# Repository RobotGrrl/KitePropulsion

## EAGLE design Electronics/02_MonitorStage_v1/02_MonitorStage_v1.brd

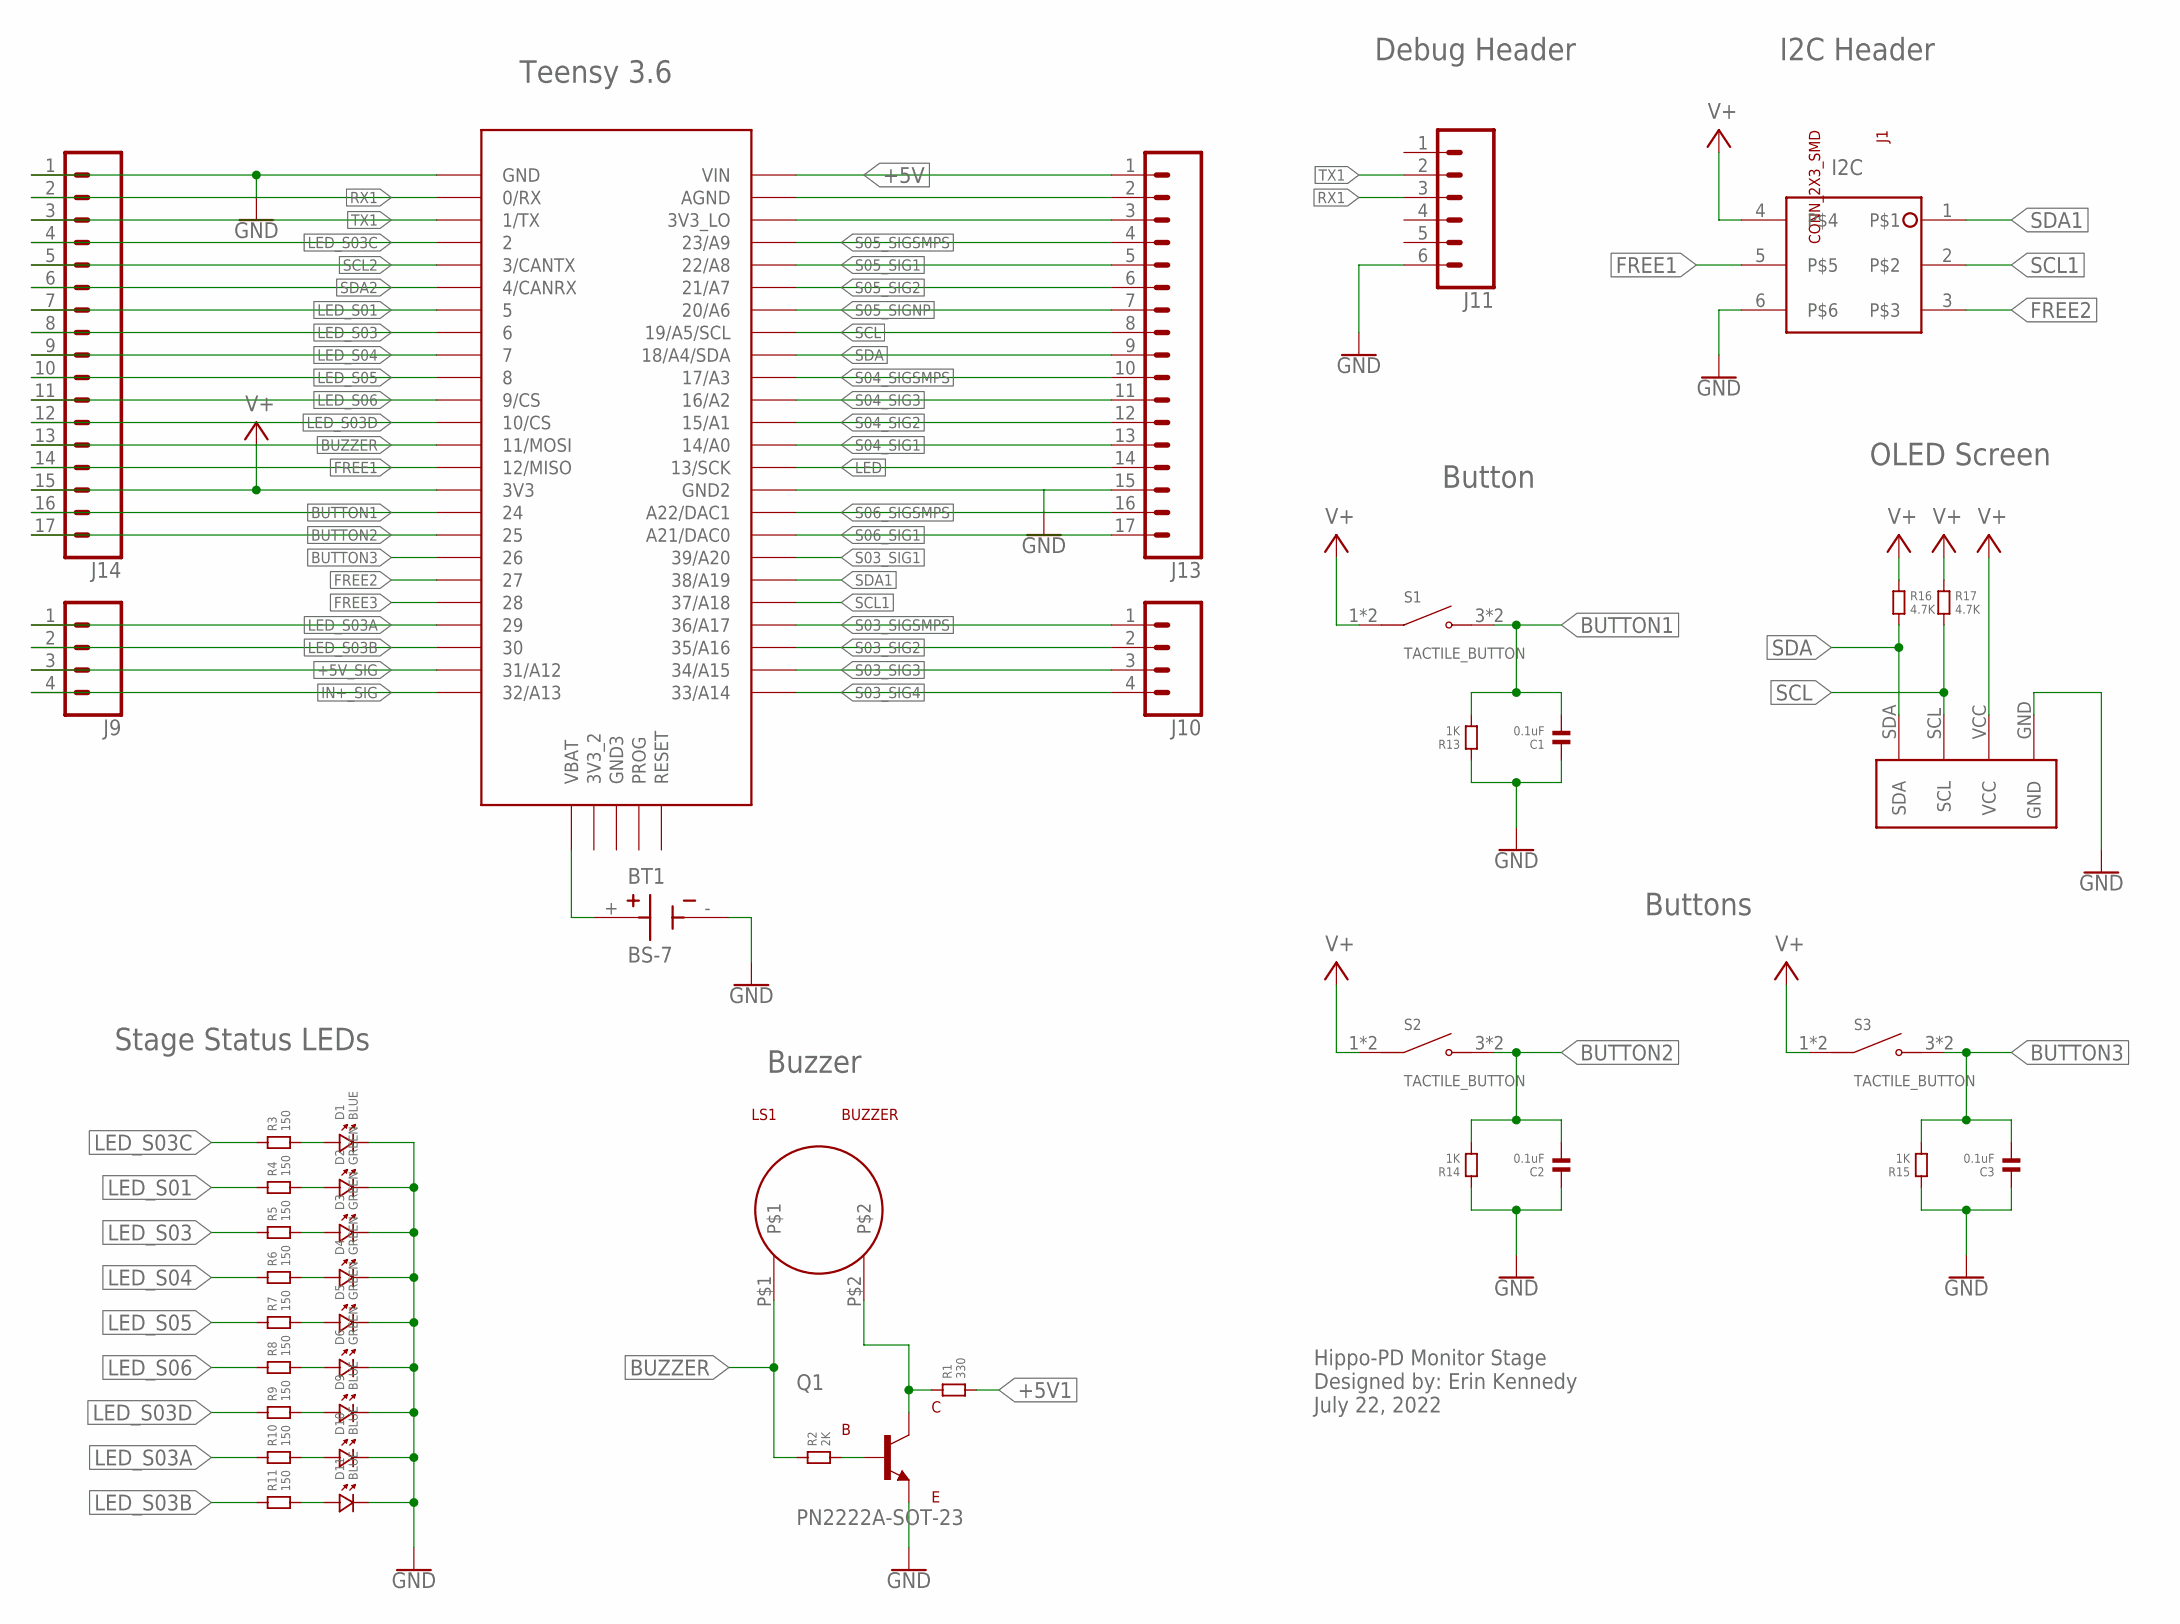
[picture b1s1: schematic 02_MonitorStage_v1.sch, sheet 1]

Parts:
BT1: BS-7; BAT_BS-7
C1, C2, C3: 0.1uF; 1206
D1, D9, D10, D11: BLUE; 1206.LED
D2, D3, D4, D5, D6: GREEN; 1206.LED
J1: CONN_2X3_SMD; 2X3_SMD_CONNECTOR
J9, J10: CONN_04; 1X04
J11: CONN_06; 1X06-SMD_RA_MALE_NO_HOLES
J13, J14: CONN_17; 1X17
LS1: BUZZER
Q1: PN2222A-SOT-23
R1: 330; 1206
R2: 2K; 1206
R3, R4, R5, R6, R7, R8, R9, R10, R11: 150; 1206
R13, R14, R15: 1K; 1206
R16, R17: 4.7K; 1206
S1, S2, S3: TACTILE_BUTTON
U1: TEENSY_3.5/3.6
U2: TINYSCREEN

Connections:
+5V: J13.1, U1.VIN; also elsewhere on the board
+5V1: R1.2
+5V_SIG: J9.3, U1.31/A12; also elsewhere on the board
BUTTON1: C1.2, J14.16, R13.2, S1.3 (NO), S1.4 (NO), U1.24
BUTTON2: C2.2, J14.17, R14.2, S2.3 (NO), S2.4 (NO), U1.25
BUTTON3: C3.2, R15.2, S3.3 (NO), S3.4 (NO), U1.26
BUZZER: J14.13, LS1.P$1, R2.1, U1.11/MOSI
FREE1: J1.5, J14.14, U1.12/MISO
FREE2: J1.3, U1.27
FREE3: U1.28
GND: BT1.-, C1.1, C2.1, C3.1, D1.P$2 (2), D2.P$2 (2), D3.P$2 (2), D4.P$2 (2), D5.P$2 (2), D6.P$2 (2), D9.P$2 (2), D10.P$2 (2), D11.P$2 (2), J1.6, J11.6, J13.15, J14.1, Q1.EMITTER, R13.1, R14.1, R15.1, U1.GND, U1.GND2, U2.GND; also elsewhere on the board
IN+_SIG: J9.4, U1.32/A13; also elsewhere on the board
LED: J13.14, U1.13/SCK
LED_S01: J14.7, R4.1, U1.5
LED_S03: J14.8, R5.1, U1.6
LED_S03A: J9.1, R10.1, U1.29
LED_S03B: J9.2, R11.1, U1.30
LED_S03C: J14.4, R3.1, U1.2
LED_S03D: J14.12, R9.1, U1.10/CS
LED_S04: J14.9, R6.1, U1.7
LED_S05: J14.10, R7.1, U1.8
LED_S06: J14.11, R8.1, U1.9/CS
unnamed: BT1.+, U1.VBAT
unnamed: D1.P$1 (1), R3.2
unnamed: D2.P$1 (1), R4.2
unnamed: J13.2, U1.AGND
unnamed: D3.P$1 (1), R5.2
unnamed: D4.P$1 (1), R6.2
unnamed: D5.P$1 (1), R7.2
unnamed: D6.P$1 (1), R8.2
unnamed: D9.P$1 (1), R9.2
unnamed: D10.P$1 (1), R10.2
unnamed: D11.P$1 (1), R11.2
unnamed: LS1.P$2, Q1.COLLECTOR, R1.1
unnamed: J13.3, U1.3V3_LO
unnamed: Q1.BASE, R2.2
RX1: J11.3, J14.2, U1.0/RX
S03_SIG1: U1.39/A20; also elsewhere on the board
S03_SIG2: J10.2, U1.35/A16; also elsewhere on the board
S03_SIG3: J10.3, U1.34/A15; also elsewhere on the board
S03_SIG4: J10.4, U1.33/A14; also elsewhere on the board
S03_SIGSMPS: J10.1, U1.36/A17; also elsewhere on the board
S04_SIG1: J13.13, U1.14/A0; also elsewhere on the board
S04_SIG2: J13.12, U1.15/A1; also elsewhere on the board
S04_SIG3: J13.11, U1.16/A2; also elsewhere on the board
S04_SIGSMPS: J13.10, U1.17/A3; also elsewhere on the board
S05_SIG1: J13.5, U1.22/A8; also elsewhere on the board
S05_SIG2: J13.6, U1.21/A7; also elsewhere on the board
S05_SIGNP: J13.7, U1.20/A6; also elsewhere on the board
S05_SIGSMPS: J13.4, U1.23/A9; also elsewhere on the board
S06_SIG1: J13.17, U1.21/DAC0 (A21/DAC0); also elsewhere on the board
S06_SIGSMPS: J13.16, U1.A22/DAC1; also elsewhere on the board
SCL: J13.8, R17.2, U1.19/A5/SCL, U2.SCL
SCL1: J1.2, U1.37/A18
SCL2: J14.5, U1.3/CANTX
SDA: J13.9, R16.2, U1.18/A4/SDA, U2.SDA
SDA1: J1.1, U1.38/A19
SDA2: J14.6, U1.4/CANRX
TX1: J11.2, J14.3, U1.1/TX
V+: J1.4, J14.15, R16.1, R17.1, S1.1 (COM), S1.2 (COM), S2.1 (COM), S2.2 (COM), S3.1 (COM), S3.2 (COM), U1.3V3, U2.VCC

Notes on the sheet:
I2C
Hippo-PD Monitor Stage Designed by: Erin Kennedy July 22, 2022
Teensy 3.6
Stage Status LEDs
Buzzer
Debug Header
I2C Header
OLED Screen
Button
Buttons

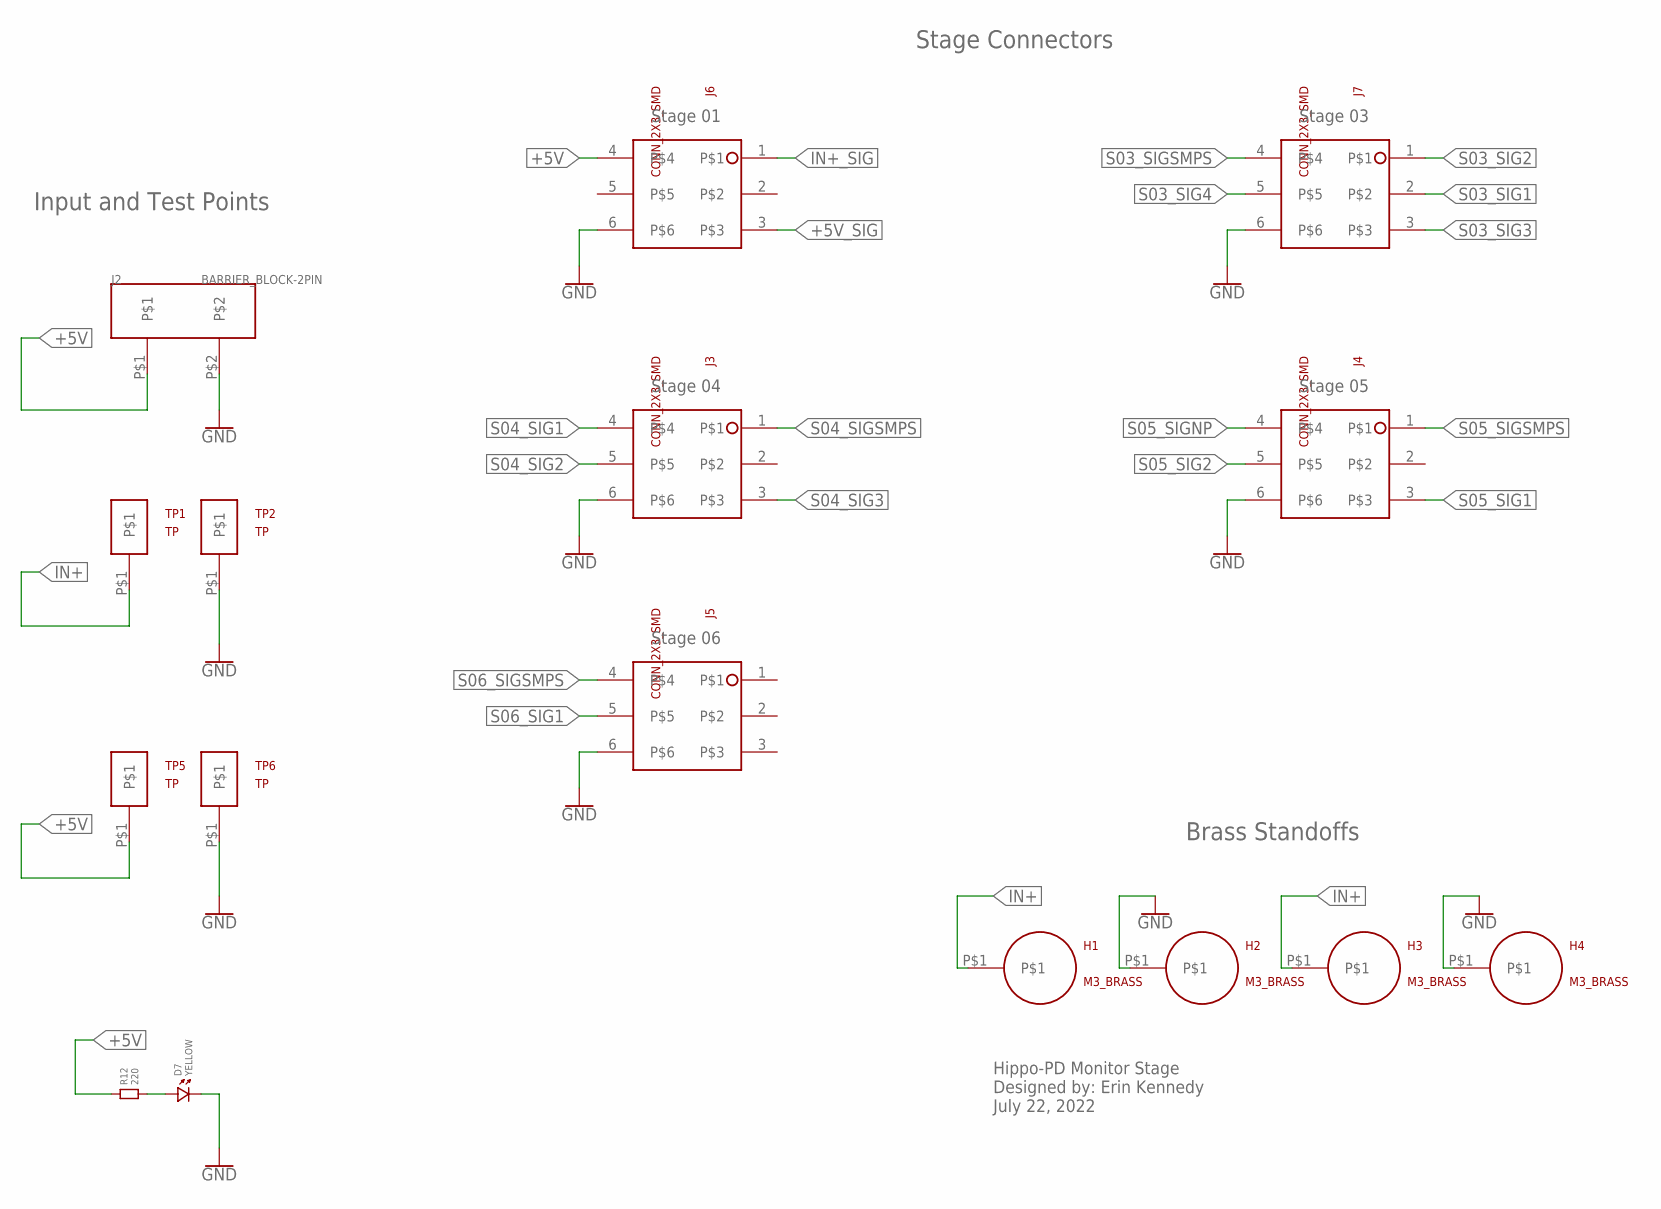
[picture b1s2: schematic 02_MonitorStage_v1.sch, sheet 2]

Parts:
D7: YELLOW; 1206.LED
H1, H2, H3, H4: M3_BRASS
J2: BARRIER_BLOCK-2PIN; BARRIERBLOCK-2PIN
J3, J4, J5, J6, J7: CONN_2X3_SMD; 2X3_SMD_CONNECTOR
R12: 220; 1206
TP1, TP2, TP5, TP6: TP

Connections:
+5V: J2.P$1, J6.4, R12.1, TP5.P$1; also elsewhere on the board
+5V_SIG: J6.3; also elsewhere on the board
GND: D7.P$2 (2), H2.P$1, H4.P$1, J2.P$2, J3.6, J4.6, J5.6, J6.6, J7.6, TP2.P$1, TP6.P$1; also elsewhere on the board
IN+: H1.P$1, H3.P$1, TP1.P$1
IN+_SIG: J6.1; also elsewhere on the board
unnamed: D7.P$1 (1), R12.2
S03_SIG1: J7.2; also elsewhere on the board
S03_SIG2: J7.1; also elsewhere on the board
S03_SIG3: J7.3; also elsewhere on the board
S03_SIG4: J7.5; also elsewhere on the board
S03_SIGSMPS: J7.4; also elsewhere on the board
S04_SIG1: J3.4; also elsewhere on the board
S04_SIG2: J3.5; also elsewhere on the board
S04_SIG3: J3.3; also elsewhere on the board
S04_SIGSMPS: J3.1; also elsewhere on the board
S05_SIG1: J4.3; also elsewhere on the board
S05_SIG2: J4.5; also elsewhere on the board
S05_SIGNP: J4.4; also elsewhere on the board
S05_SIGSMPS: J4.1; also elsewhere on the board
S06_SIG1: J5.5; also elsewhere on the board
S06_SIGSMPS: J5.4; also elsewhere on the board

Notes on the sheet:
Stage 01
Stage 03
Stage 04
Stage 05
Stage 06
Hippo-PD Monitor Stage Designed by: Erin Kennedy July 22, 2022
Input and Test Points
Brass Standoffs
Stage Connectors

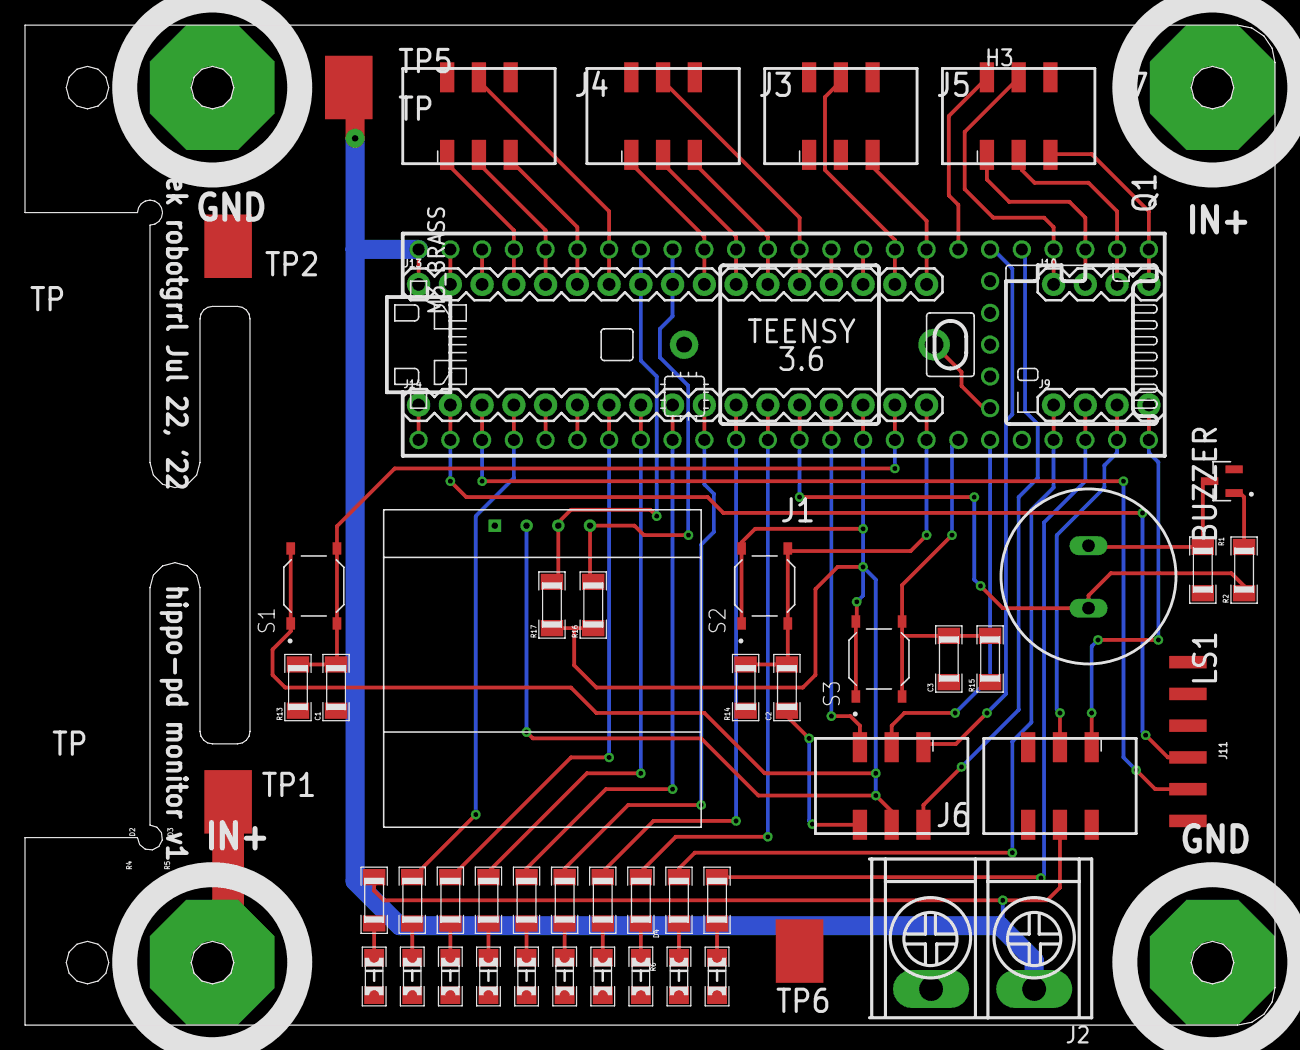
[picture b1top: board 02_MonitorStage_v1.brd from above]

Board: 2 copper layers, 100.0 x 80.0 mm, 58 parts (1 on the bottom side), 60 nets.

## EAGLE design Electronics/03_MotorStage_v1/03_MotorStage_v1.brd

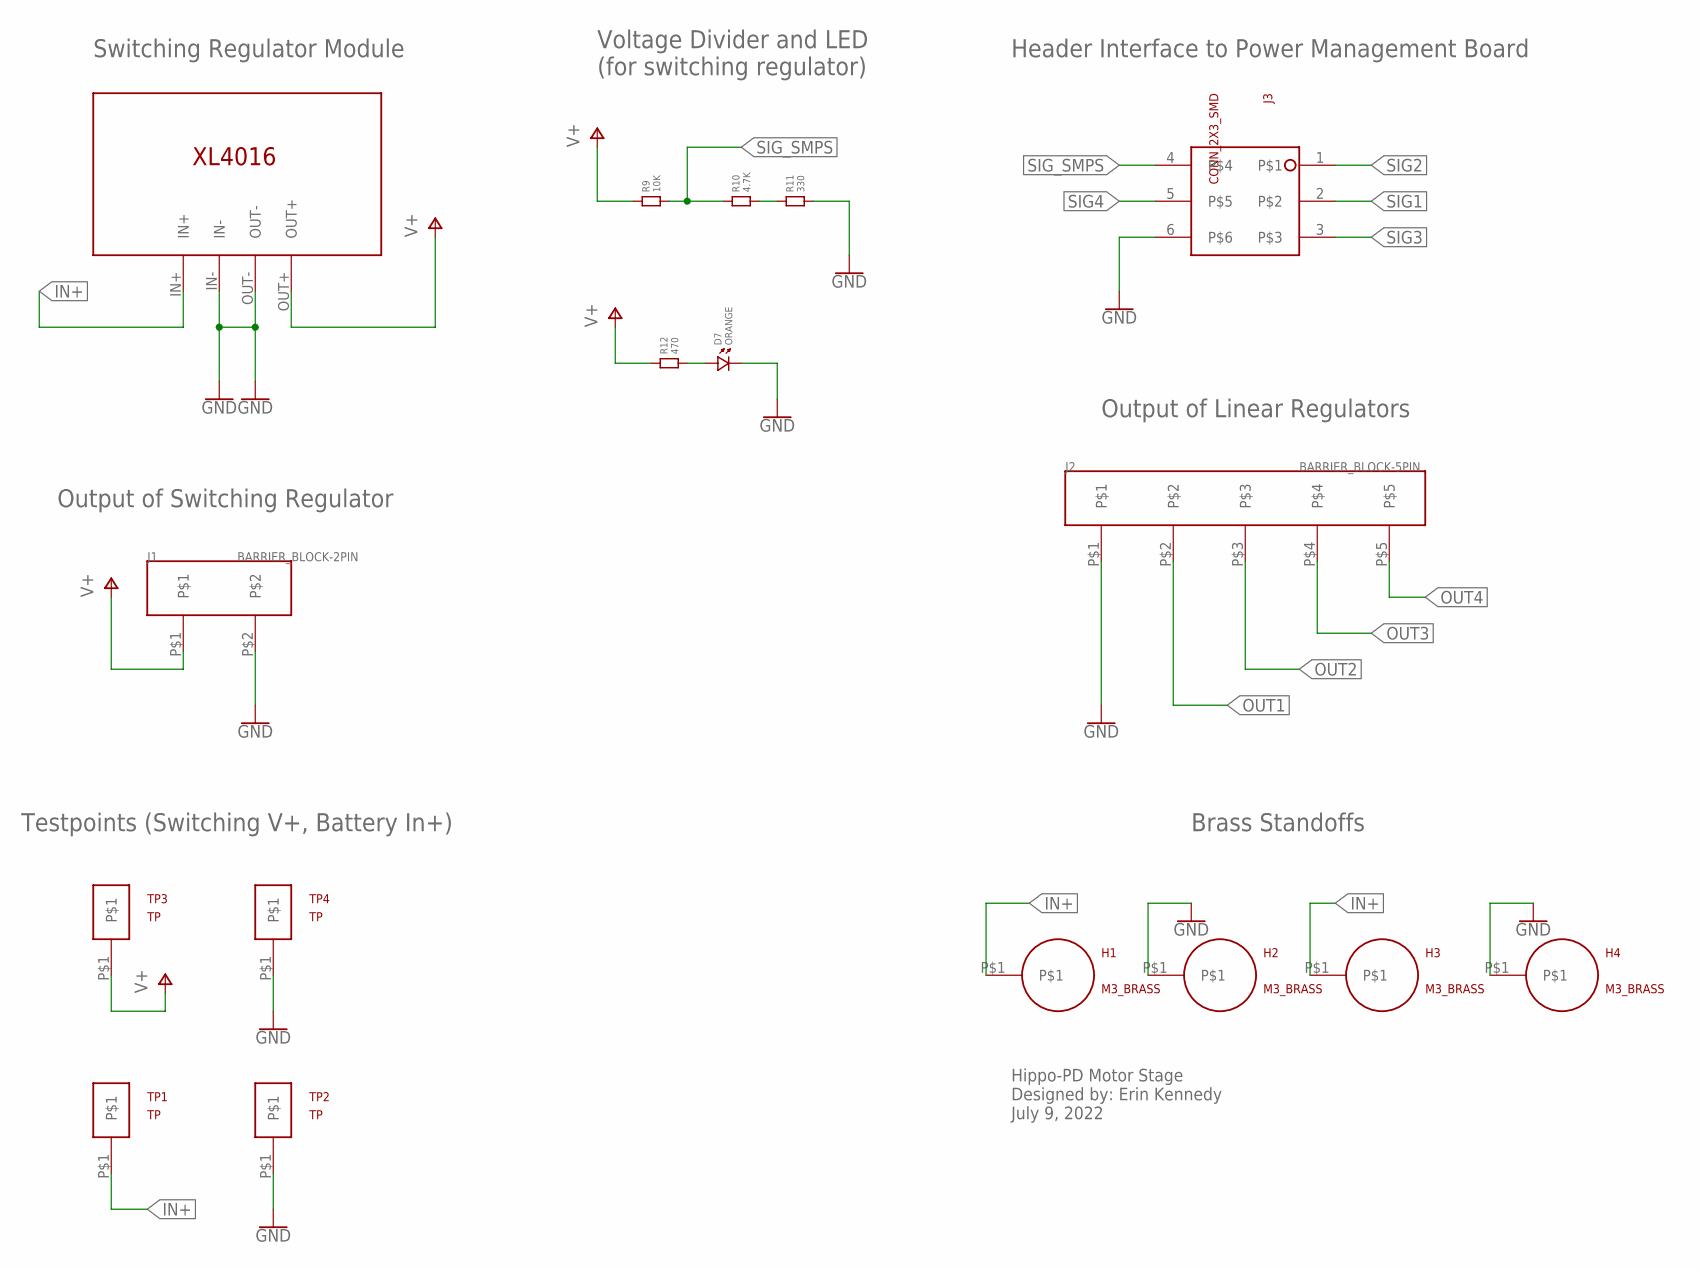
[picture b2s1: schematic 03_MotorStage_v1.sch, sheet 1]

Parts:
D7: ORANGE; 1206.LED
H1, H2, H3, H4: M3_BRASS
J1: BARRIER_BLOCK-2PIN; BARRIERBLOCK-2PIN
J2: BARRIER_BLOCK-5PIN; BARRIERBLOCK-5PIN
J3: CONN_2X3_SMD; 2X3_SMD_CONNECTOR
R9: 10K; 1206
R10: 4.7K; 1206
R11: 330; 1206
R12: 470; 1206
TP1, TP2, TP3, TP4: TP
U1: XL4016-DEV

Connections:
GND: D7.P$2 (2), H2.P$1, H4.P$1, J1.P$2, J2.P$1, J3.6, R11.2, TP2.P$1, TP4.P$1, U1.IN-, U1.OUT-; also elsewhere on the board
IN+: H1.P$1, H3.P$1, TP1.P$1, U1.IN+
unnamed: D7.P$1 (1), R12.2
unnamed: R10.2, R11.1
OUT1: J2.P$2; also elsewhere on the board
OUT2: J2.P$3; also elsewhere on the board
OUT3: J2.P$4; also elsewhere on the board
OUT4: J2.P$5; also elsewhere on the board
SIG1: J3.2; also elsewhere on the board
SIG2: J3.1; also elsewhere on the board
SIG3: J3.3; also elsewhere on the board
SIG4: J3.5; also elsewhere on the board
SIG_SMPS: J3.4, R9.2, R10.1
V+: J1.P$1, R9.1, R12.1, TP3.P$1, U1.OUT+; also elsewhere on the board

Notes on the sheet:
Switching Regulator Module
Voltage Divider and LED (for switching regulator)
Header Interface to Power Management Board
Output of Linear Regulators
Brass Standoffs
Testpoints (Switching V+, Battery In+)
Output of Switching Regulator
Hippo-PD Motor Stage Designed by: Erin Kennedy July 9, 2022

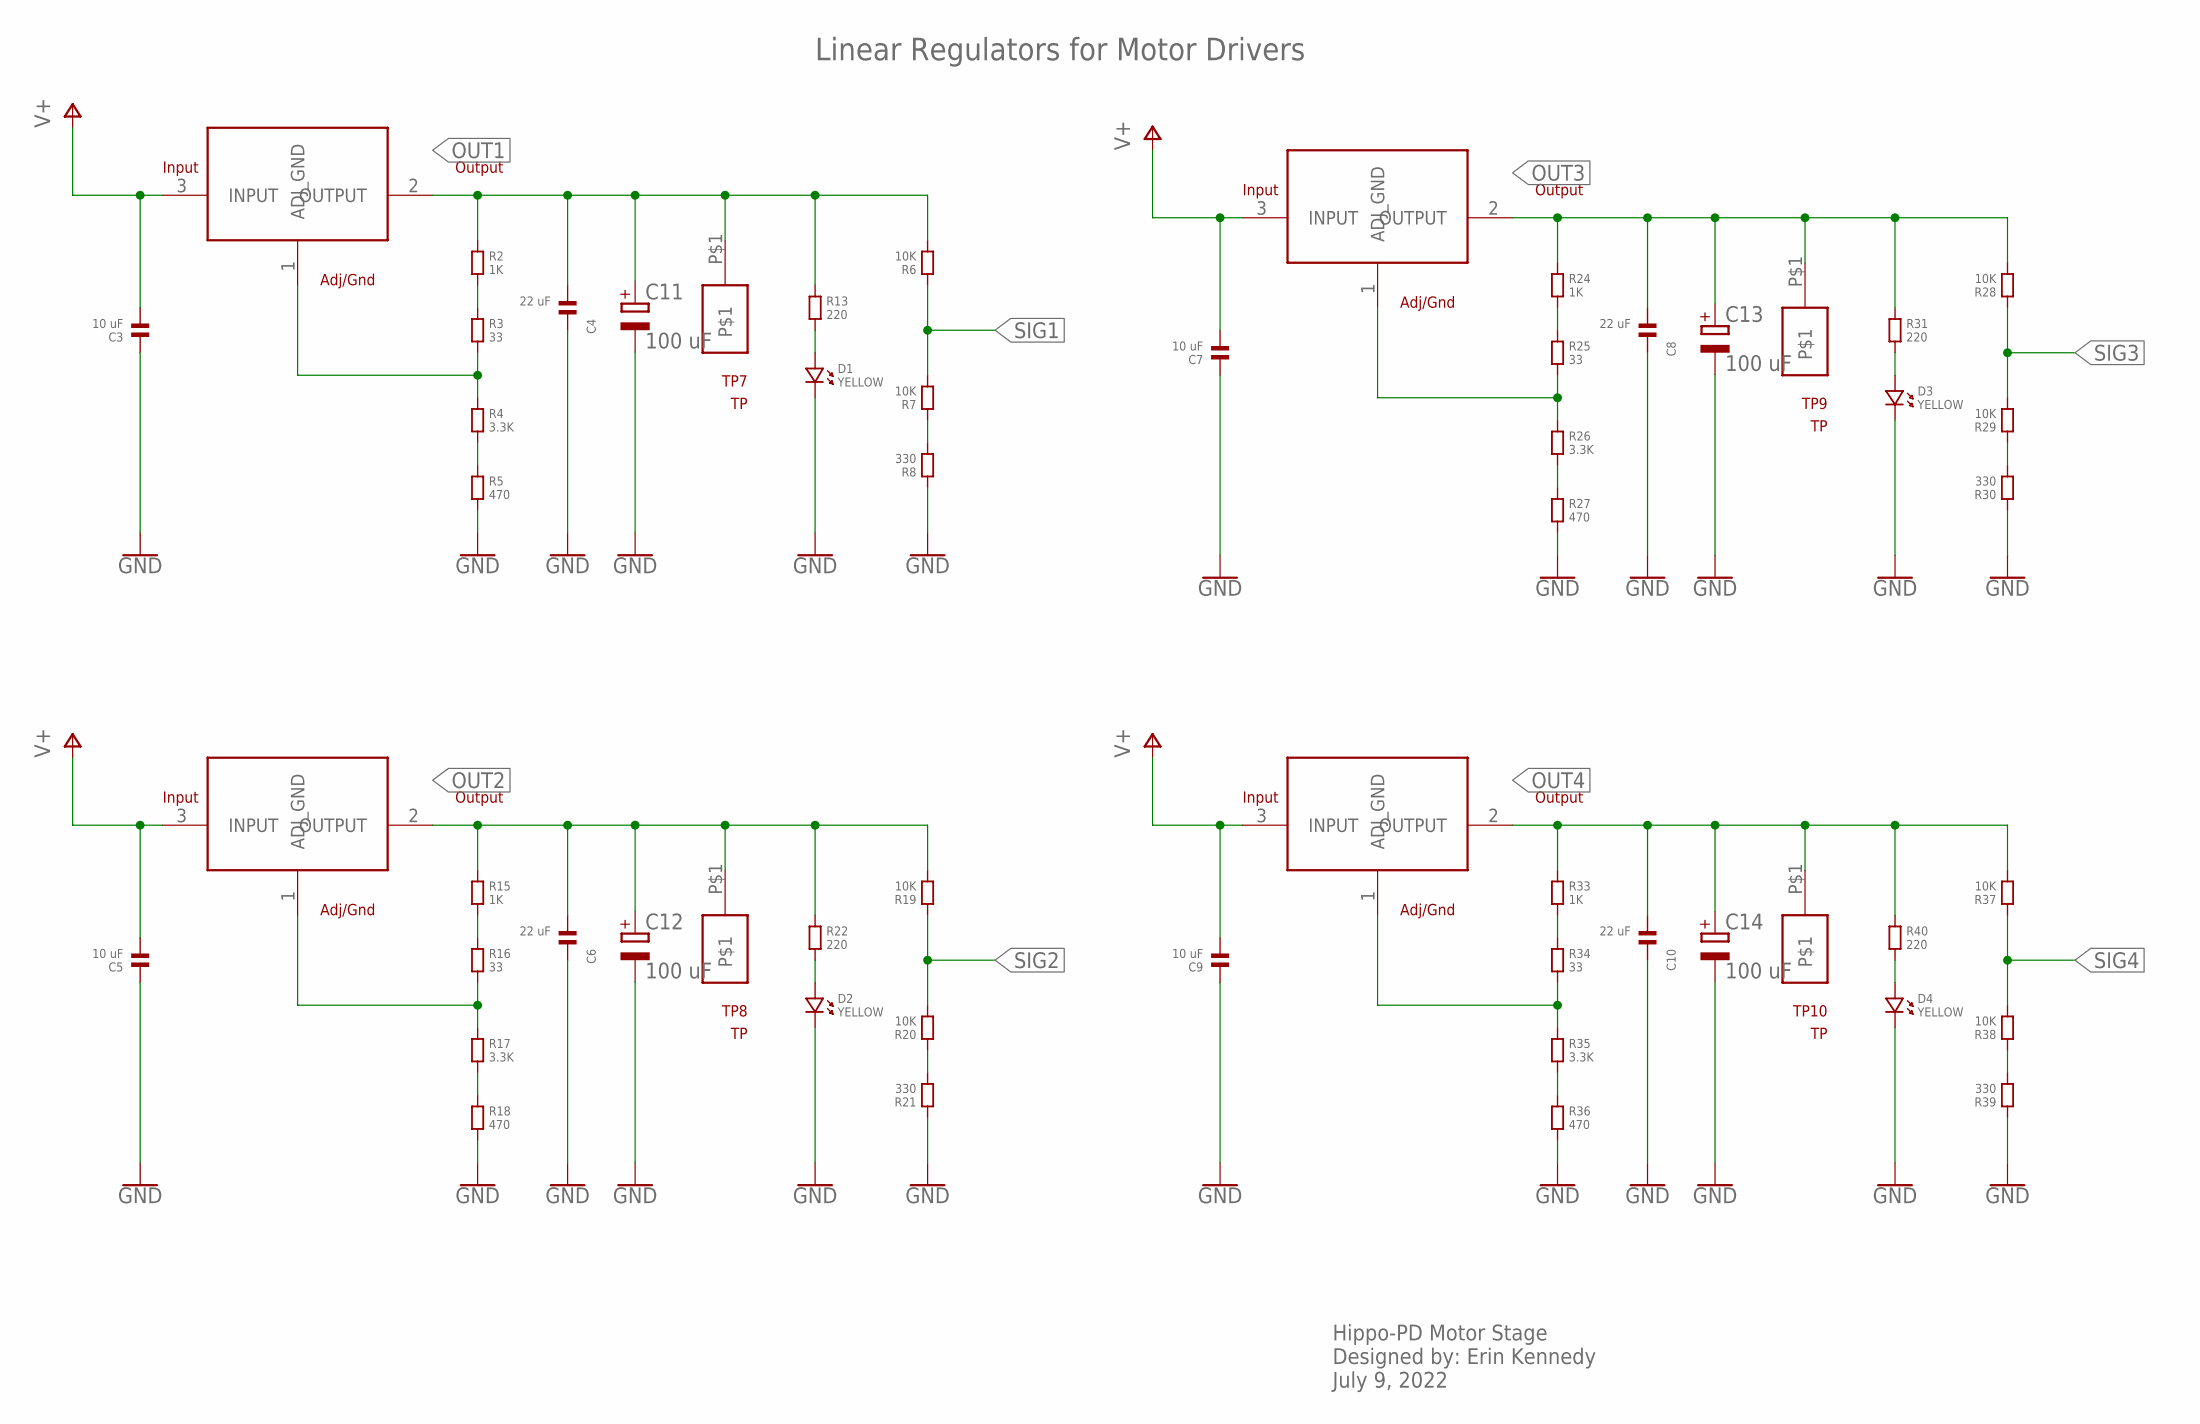
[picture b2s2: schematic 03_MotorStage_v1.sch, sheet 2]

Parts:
C3, C5, C7, C9: 10 uF; 1206
C4, C6, C8, C10: 22 uF; 1206
C11, C12, C13, C14: 100 uF; ELECTROLYTIC_CAP
D1, D2, D3, D4: YELLOW; 1206.LED
R2, R15, R24, R33: 1K; 1206
R3, R16, R25, R34: 33; 1206
R4, R17, R26, R35: 3.3K; 1206
R5, R18, R27, R36: 470; 1206
R6, R7, R19, R20, R28, R29, R37, R38: 10K; 1206
R8, R21, R30, R39: 330; 1206
R13, R22, R31, R40: 220; 1206
TP7, TP8, TP9, TP10: TP
U2, U3, U4, U5: AZ1084C

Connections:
GND: C3.1, C4.1, C5.1, C6.1, C7.1, C8.1, C9.1, C10.1, C11.-, C12.-, C13.-, C14.-, D1.P$2 (2), D2.P$2 (2), D3.P$2 (2), D4.P$2 (2), R5.2, R8.1, R18.2, R21.1, R27.2, R30.1, R36.2, R39.1; also elsewhere on the board
unnamed: D1.P$1 (1), R13.2
unnamed: R2.2, R3.1
unnamed: R3.2, R4.1, U2.1 (ADJ_GND)
unnamed: R4.2, R5.1
unnamed: D3.P$1 (1), R31.2
unnamed: R7.1, R8.2
unnamed: R24.2, R25.1
unnamed: D2.P$1 (1), R22.2
unnamed: R15.2, R16.1
unnamed: R16.2, R17.1, U3.1 (ADJ_GND)
unnamed: R17.2, R18.1
unnamed: R20.1, R21.2
unnamed: R25.2, R26.1, U4.1 (ADJ_GND)
unnamed: R26.2, R27.1
unnamed: R29.1, R30.2
unnamed: D4.P$1 (1), R40.2
unnamed: R33.2, R34.1
unnamed: R34.2, R35.1, U5.1 (ADJ_GND)
unnamed: R35.2, R36.1
unnamed: R38.1, R39.2
OUT1: C4.2, C11.+, R2.1, R6.2, R13.1, TP7.P$1, U2.2 (OUTPUT); also elsewhere on the board
OUT2: C6.2, C12.+, R15.1, R19.2, R22.1, TP8.P$1, U3.2 (OUTPUT); also elsewhere on the board
OUT3: C8.2, C13.+, R24.1, R28.2, R31.1, TP9.P$1, U4.2 (OUTPUT); also elsewhere on the board
OUT4: C10.2, C14.+, R33.1, R37.2, R40.1, TP10.P$1, U5.2 (OUTPUT); also elsewhere on the board
SIG1: R6.1, R7.2; also elsewhere on the board
SIG2: R19.1, R20.2; also elsewhere on the board
SIG3: R28.1, R29.2; also elsewhere on the board
SIG4: R37.1, R38.2; also elsewhere on the board
V+: C3.2, C5.2, C7.2, C9.2, U2.3 (INPUT), U3.3 (INPUT), U4.3 (INPUT), U5.3 (INPUT); also elsewhere on the board

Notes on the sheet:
Linear Regulators for Motor Drivers
Hippo-PD Motor Stage Designed by: Erin Kennedy July 9, 2022

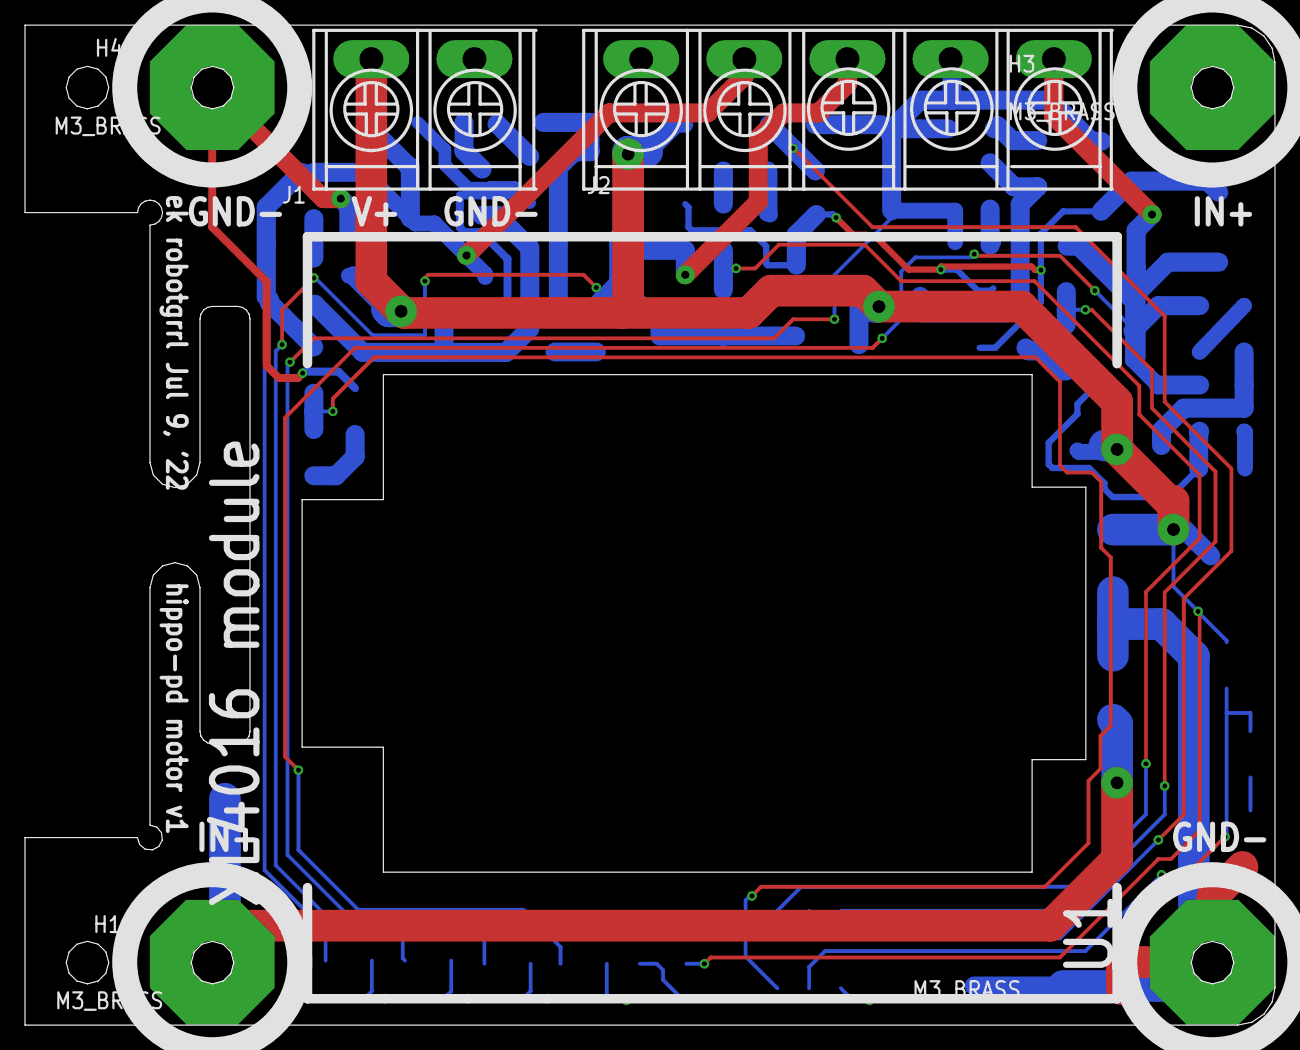
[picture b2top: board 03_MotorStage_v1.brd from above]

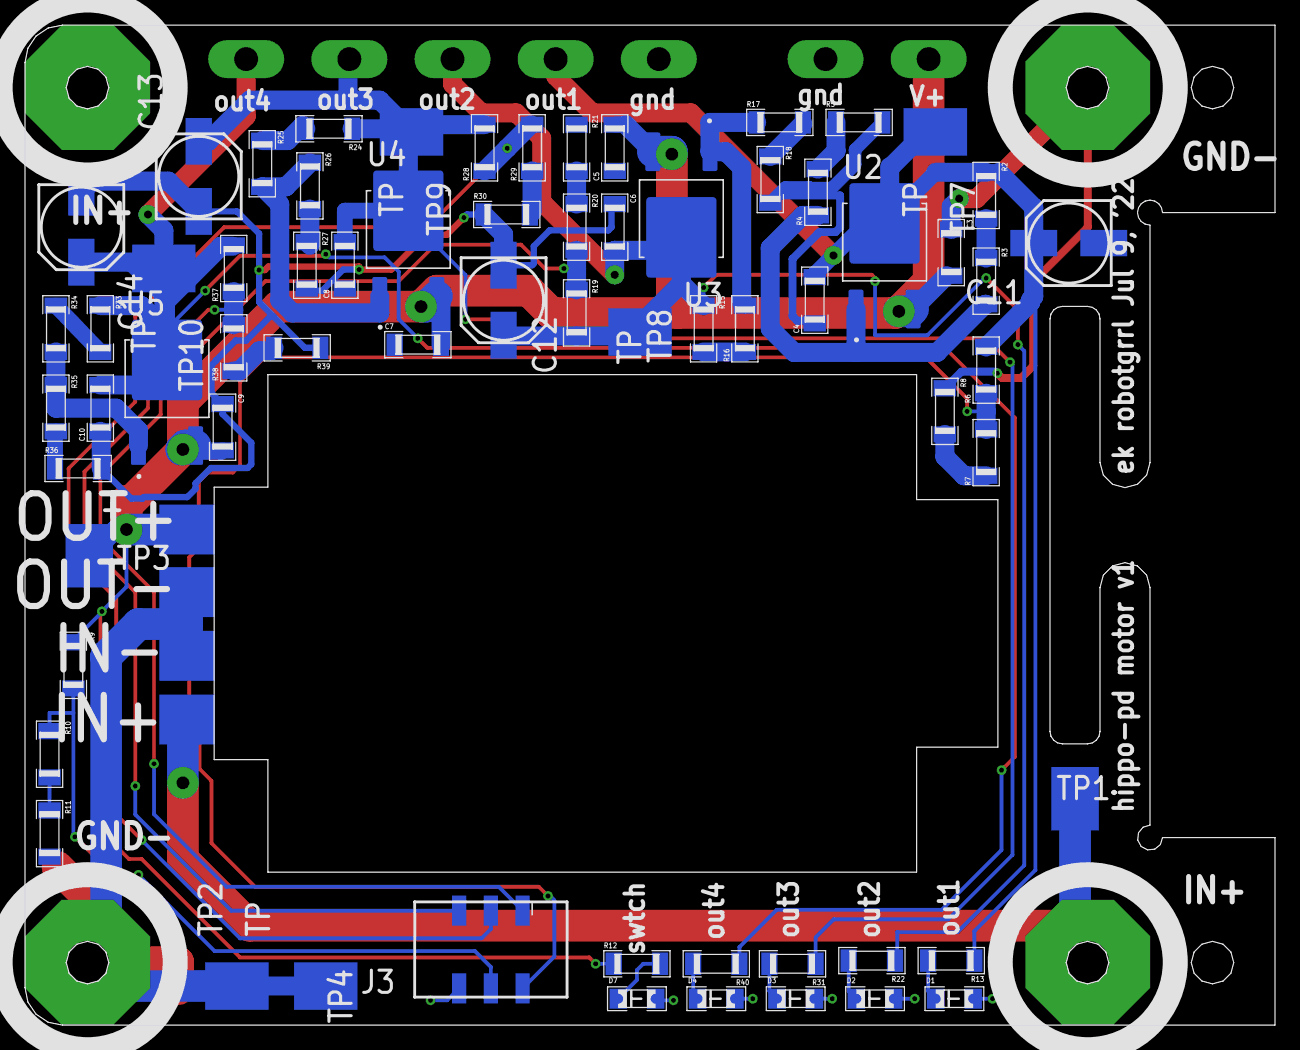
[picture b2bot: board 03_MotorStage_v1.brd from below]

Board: 2 copper layers, 100.0 x 80.0 mm, 73 parts (66 on the bottom side), 34 nets.

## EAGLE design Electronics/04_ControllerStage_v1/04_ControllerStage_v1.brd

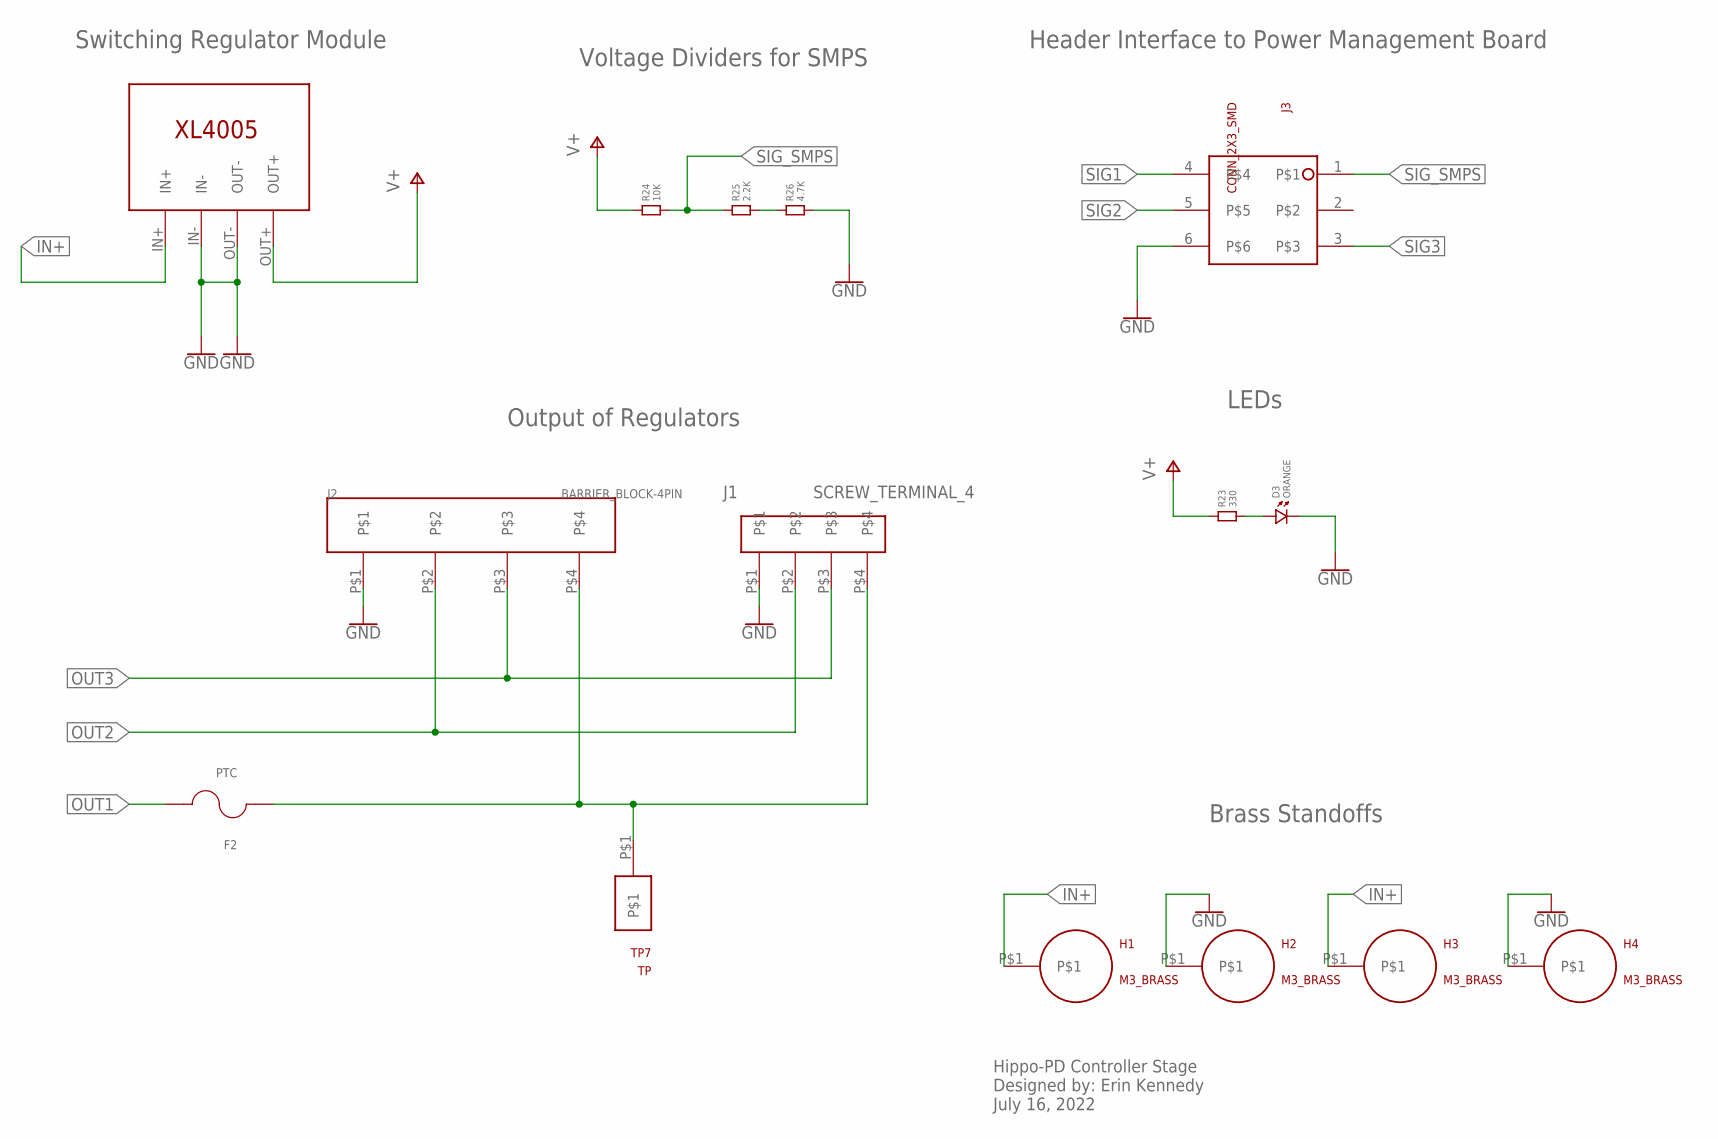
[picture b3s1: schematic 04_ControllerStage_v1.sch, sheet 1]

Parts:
D3: ORANGE; 1206.LED
F2: PTC
H1, H2, H3, H4: M3_BRASS
J1: SCREW_TERMINAL_4; SCREW_TERM_4
J2: BARRIER_BLOCK-4PIN; BARRIERBLOCK-4PIN
J3: CONN_2X3_SMD; 2X3_SMD_CONNECTOR
R23: 330; 1206
R24: 10K; 1206
R25: 2.2K; 1206
R26: 4.7K; 1206
TP7: TP
U1: XL4005-DEV

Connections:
GND: D3.P$2 (2), H2.P$1, H4.P$1, J1.P$1, J2.P$1, J3.6, R26.2, U1.IN-, U1.OUT-; also elsewhere on the board
IN+: H1.P$1, H3.P$1, U1.IN+; also elsewhere on the board
unnamed: D3.P$1 (1), R23.2
unnamed: R25.2, R26.1
unnamed: F2.1, J1.P$4, J2.P$4, TP7.P$1
OUT1: F2.2; also elsewhere on the board
OUT2: J1.P$2, J2.P$2; also elsewhere on the board
OUT3: J1.P$3, J2.P$3; also elsewhere on the board
SIG1: J3.4; also elsewhere on the board
SIG2: J3.5; also elsewhere on the board
SIG3: J3.3; also elsewhere on the board
SIG_SMPS: J3.1, R24.2, R25.1
V+: R23.1, R24.1, U1.OUT+; also elsewhere on the board

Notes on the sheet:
Switching Regulator Module
Voltage Dividers for SMPS
Header Interface to Power Management Board
Output of Regulators
Brass Standoffs
Hippo-PD Controller Stage Designed by: Erin Kennedy July 16, 2022
LEDs

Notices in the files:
parts and their libraries:
SparkFun-Connectors: Licensing: Creative Commons ShareAlike 4.0 International - https://creativecommons.org/licenses/by-sa/4.0
COPYRIGHT: Copyright (C) 2022 Ultra Librarian. All rights reserved.
